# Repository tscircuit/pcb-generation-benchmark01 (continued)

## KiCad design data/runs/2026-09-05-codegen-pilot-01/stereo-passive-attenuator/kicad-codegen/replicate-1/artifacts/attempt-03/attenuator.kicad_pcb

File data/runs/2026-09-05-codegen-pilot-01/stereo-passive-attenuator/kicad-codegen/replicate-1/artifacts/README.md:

# Stereo AC-coupled attenuator

Final entry files: `attempt-03/attenuator.kicad_pro`, `attempt-03/attenuator.kicad_sch`, and `attempt-03/attenuator.kicad_pcb`. Editable generation source is `attempt-03/generate.py`. The final candidate includes local symbol and footprint library tables and the standard library subsets it uses. The generator itself reads the installed KiCad 10 libraries at the macOS path recorded in its source.

Method: native KiCad schematic S-expression generation and KiCad Python `pcbnew` board generation, using only shell tools. No GUI, tscircuit, evaluator references, or reference designs were used. All copper routes are explicit tracks; ground uses the back copper layer with through vias. A rule file enforces 0.25 mm minimum clearance and trace width; actual signal tracks are 0.30 mm.

J1/J2 use standard 2.54 mm 1x03 through-hole headers. Pin 1 is left signal, pin 2 is shared GND, and pin 3 is right signal. Connector pin numbers and signal names are marked on front silkscreen. Both footprint origins are 3 mm from their respective board edges; their geometric body centres share that same x position.

C1/C2 are nonpolar 1 uF ceramic capacitors with 0805 footprints, pin 1 input and pin 2 internal AC node. R1/R3 are 10 kohm 0805 series resistors, pin 1 internal AC node and pin 2 output. R2/R4 are 10 kohm 0805 shunt resistors, pin 1 output and pin 2 GND. TP1/TP2/TP3 are separate exposed 1.5 mm front copper pads for LEFT_OUT/RIGHT_OUT/GND. Net names in the native PCB carry KiCad's root-sheet `/` prefix to match schematic local labels.

The board outline is 50 x 30 mm with two copper layers. Left components are above the board midpoint and right components below it. All required nets are routed. Native schematic SVG/netlist and board SVG exports are retained in the final attempt. ERC and schematic-parity DRC report zero errors, zero warnings, zero unconnected pads, and zero footprint errors. Raw logs and the independent schematic-netlist/PCB connectivity and geometry check are in `../logs/`.

Attempt 01 was fully generated and routed, but had library-table, net-name parity, and silkscreen warnings. Attempt 02 is preserved as a failed repair: a KiCad SWIG UTF8 setter TypeError stopped generation after schematic output. Attempt 03 fixes that API call and passes validation. Each attempt remains separate; no candidate was overwritten.

Limitations: no physical testing, manufacturing exports, signal simulation, component voltage ratings, tolerance selection, or part-number procurement validation. Capacitor value and dielectric type are documented, but exact manufacturer parts are unspecified by the prompt. The bundled KiCad Python runtime emitted a wxApp assertion diagnostic during generation; it did not prevent the final native files or successful native CLI checks. SVG exports were generated but not visually inspected. Default KiCad ignored-check lists are preserved verbatim in the native reports; no violation exclusions were added.

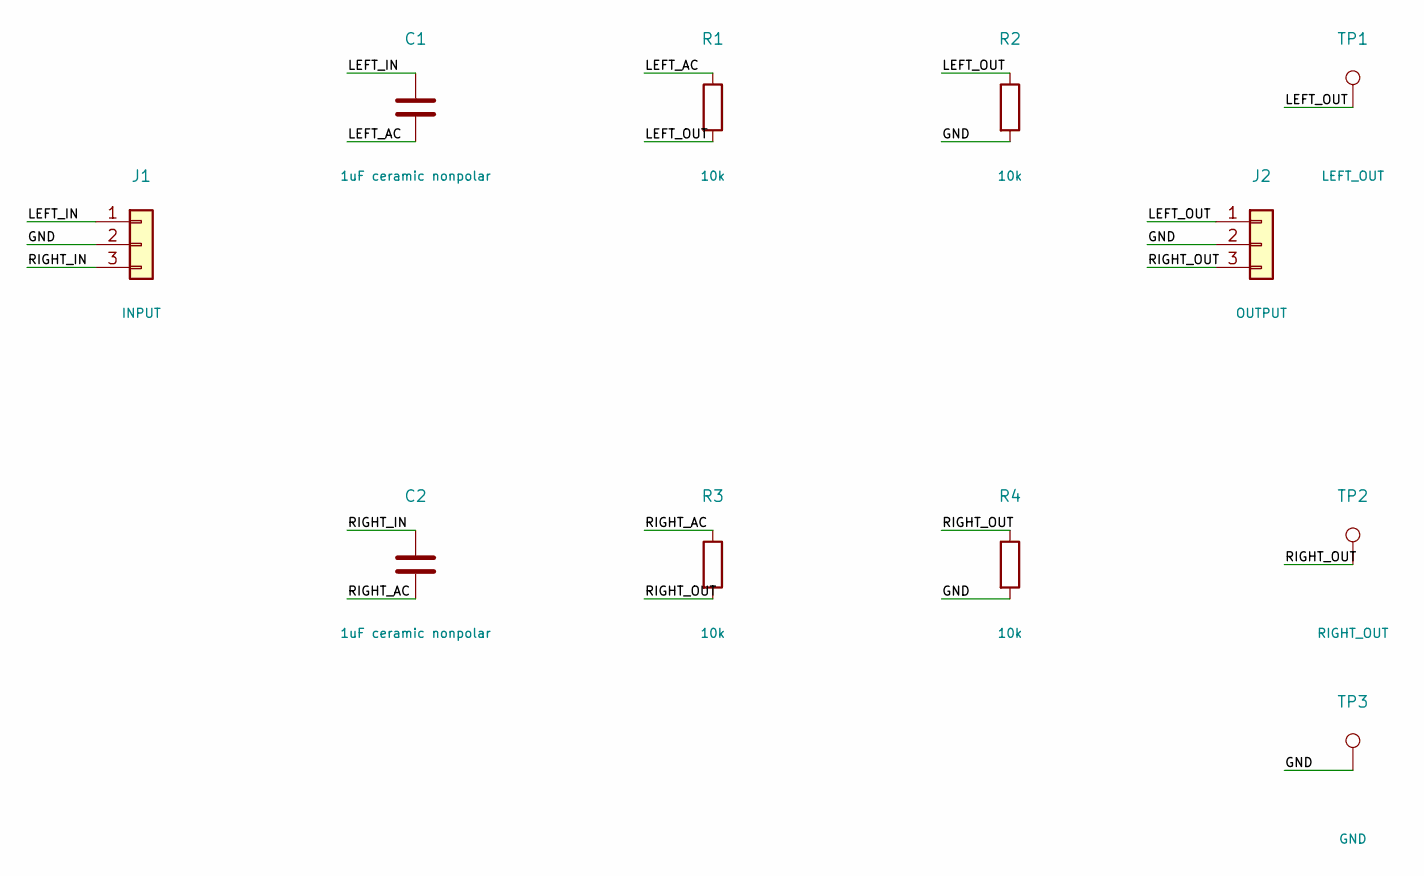
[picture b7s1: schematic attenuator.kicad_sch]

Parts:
C1, C2: 1uF ceramic nonpolar; C_0805_2012Metric
J1: INPUT; PinHeader_1x03_P2.54mm_Vertical
J2: OUTPUT; PinHeader_1x03_P2.54mm_Vertical
R1, R2, R3, R4: 10k; R_0805_2012Metric
TP1: LEFT_OUT; TestPoint_Pad_D1.5mm
TP2: RIGHT_OUT; TestPoint_Pad_D1.5mm
TP3: GND; TestPoint_Pad_D1.5mm

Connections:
/GND: J1.2, J2.2, R2.2, R4.2, TP3.1
/LEFT_AC: C1.2, R1.1
/LEFT_IN: C1.1, J1.1
/LEFT_OUT: J2.1, R1.2, R2.1, TP1.1
/RIGHT_AC: C2.2, R3.1
/RIGHT_IN: C2.1, J1.3
/RIGHT_OUT: J2.3, R3.2, R4.1, TP2.1

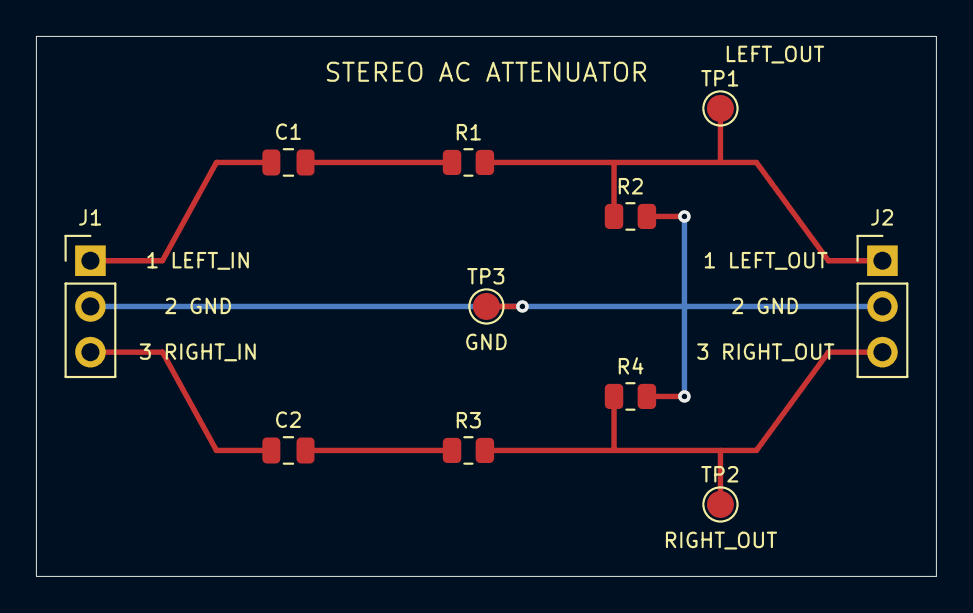
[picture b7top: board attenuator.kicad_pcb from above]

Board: 2 copper layers, 50.0 x 30.0 mm, 11 parts (0 on the bottom side), 7 nets.

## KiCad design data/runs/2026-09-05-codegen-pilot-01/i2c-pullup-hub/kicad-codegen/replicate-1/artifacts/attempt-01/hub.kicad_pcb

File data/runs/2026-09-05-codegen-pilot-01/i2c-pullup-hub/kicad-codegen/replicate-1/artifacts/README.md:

# I2C pull-up hub — KiCad code generation

Final entry files are `attempt-02/hub.kicad_pro`, `attempt-02/hub.kicad_sch`, and `attempt-02/hub.kicad_pcb`. Open the project in KiCad 10. The schematic, footprints, copper routes, vias, outline, and silkscreen are native editable objects. `attempt-02/generate.py` is the retained editable generation source. The adjacent library tables and `libraries/` directory include the exact standard symbols and footprints used.

J1/J2/J3 use standard 1×4 vertical 2.54 mm through-hole header footprints. All map 1=+3V3, 2=GND, 3=SDA, 4=SCL. C1/C2/C3 are 100 nF in 0805 footprints and sit 3.8 mm from their connector's geometric centre. R1/R2 are 4.7 kohm in 0805 footprints. Their pad 1 connects +3V3; pad 2 connects to the corresponding solder-jumper pad 1. Jumper pad 2 connects SDA or SCL. JP1/JP2 use the standard 1.3 mm pitch open solder-jumper footprint with 1.0×1.5 mm rectangular pads, leaving a 0.30 mm copper gap. Pull-ups are disabled until the user solders the respective jumper.

The outline is 45×35 mm. Copper has two layers with 0.25 mm traces and minimum 0.25 mm clearance rules; vias are 0.60 mm with 0.30 mm drills. Connector centres are 3 mm from their required edges. The generation method used direct native schematic S-expressions with standard embedded symbols and KiCad Python `pcbnew` bindings for the board, with a clearance-aware two-layer grid maze router. No GUI operations, tscircuit, external designs, or evaluator references were used.

Attempt 01 is preserved with its failed reports: ERC library/grid warnings, PCB metadata parity warnings, and silkscreen warnings. Attempt 02 repairs grid alignment, library resolution, footprint/net metadata, and silkscreen placement/size. Native ERC and DRC (including schematic parity) both report zero violations for attempt 02. DRC reports zero unconnected items. Native schematic SVG, netlist, and PCB SVG exports succeeded. Exact validation commands are in `../logs/validate.sh` and `../logs/validate-02.sh`; raw reports are in `../logs/attempt-0*-*.json` and `*.log`. Geometry/netlist measurements are in `../logs/attempt-02-geometry.json`.

No known unresolved circuit/layout requirement was detected by the performed checks. Physical testing, fabrication, assembly, and visual rendering review were not performed. The routing uses numerous short native segments; it remains editable. Absolute KiCad installation path in the generator may need adjustment on another system; native project library references are relative.

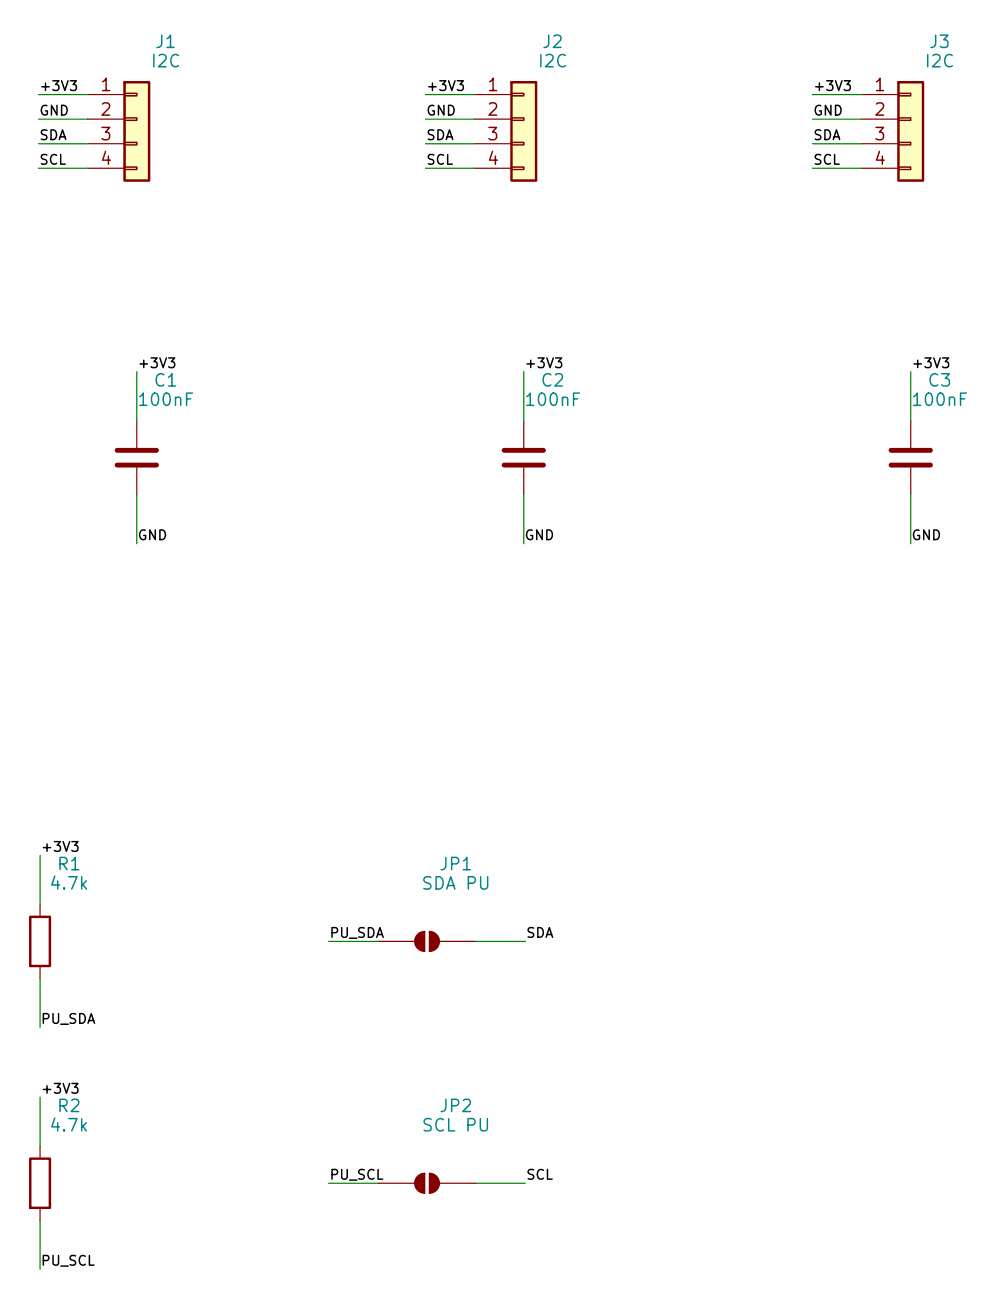
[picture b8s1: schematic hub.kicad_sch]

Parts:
C1, C2, C3: 100nF; C_0805_2012Metric
J1, J2, J3: I2C; PinHeader_1x04_P2.54mm_Vertical
JP1: SDA PU; SolderJumper-2_P1.3mm_Open_Pad1.0x1.5mm
JP2: SCL PU; SolderJumper-2_P1.3mm_Open_Pad1.0x1.5mm
R1, R2: 4.7k; R_0805_2012Metric

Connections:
+3V3: C1.1, C2.1, C3.1, J1.1, J2.1, J3.1, R1.1, R2.1
GND: C1.2, C2.2, C3.2, J1.2, J2.2, J3.2
PU_SCL: JP2.1 (A), R2.2
PU_SDA: JP1.1 (A), R1.2
SCL: J1.4, J2.4, J3.4, JP2.2 (B)
SDA: J1.3, J2.3, J3.3, JP1.2 (B)

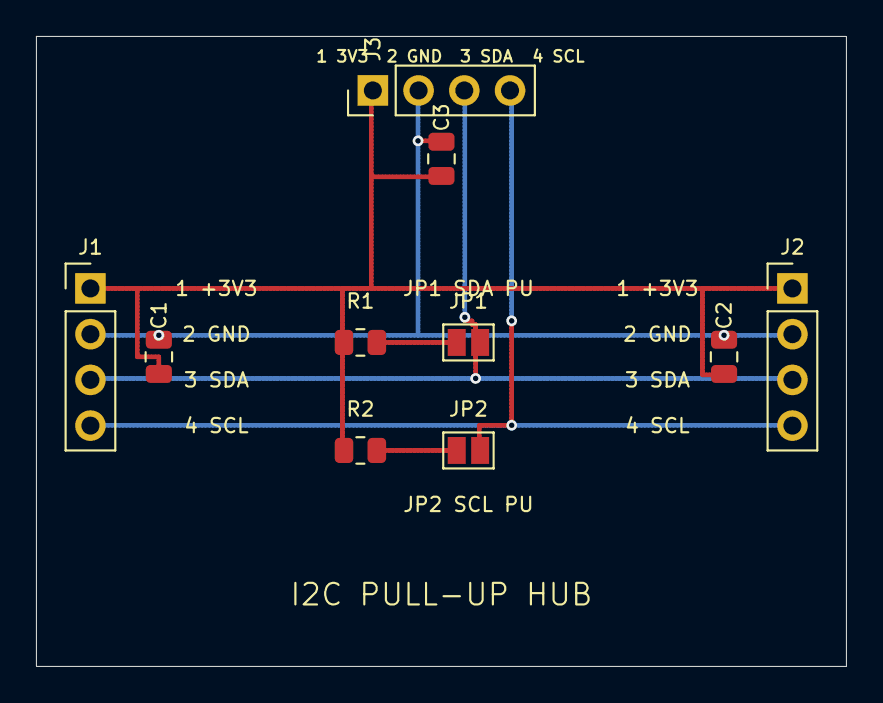
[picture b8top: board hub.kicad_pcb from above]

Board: 2 copper layers, 45.0 x 35.0 mm, 10 parts (0 on the bottom side), 6 nets.
